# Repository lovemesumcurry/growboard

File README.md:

# growboard
 first keyboard PCB

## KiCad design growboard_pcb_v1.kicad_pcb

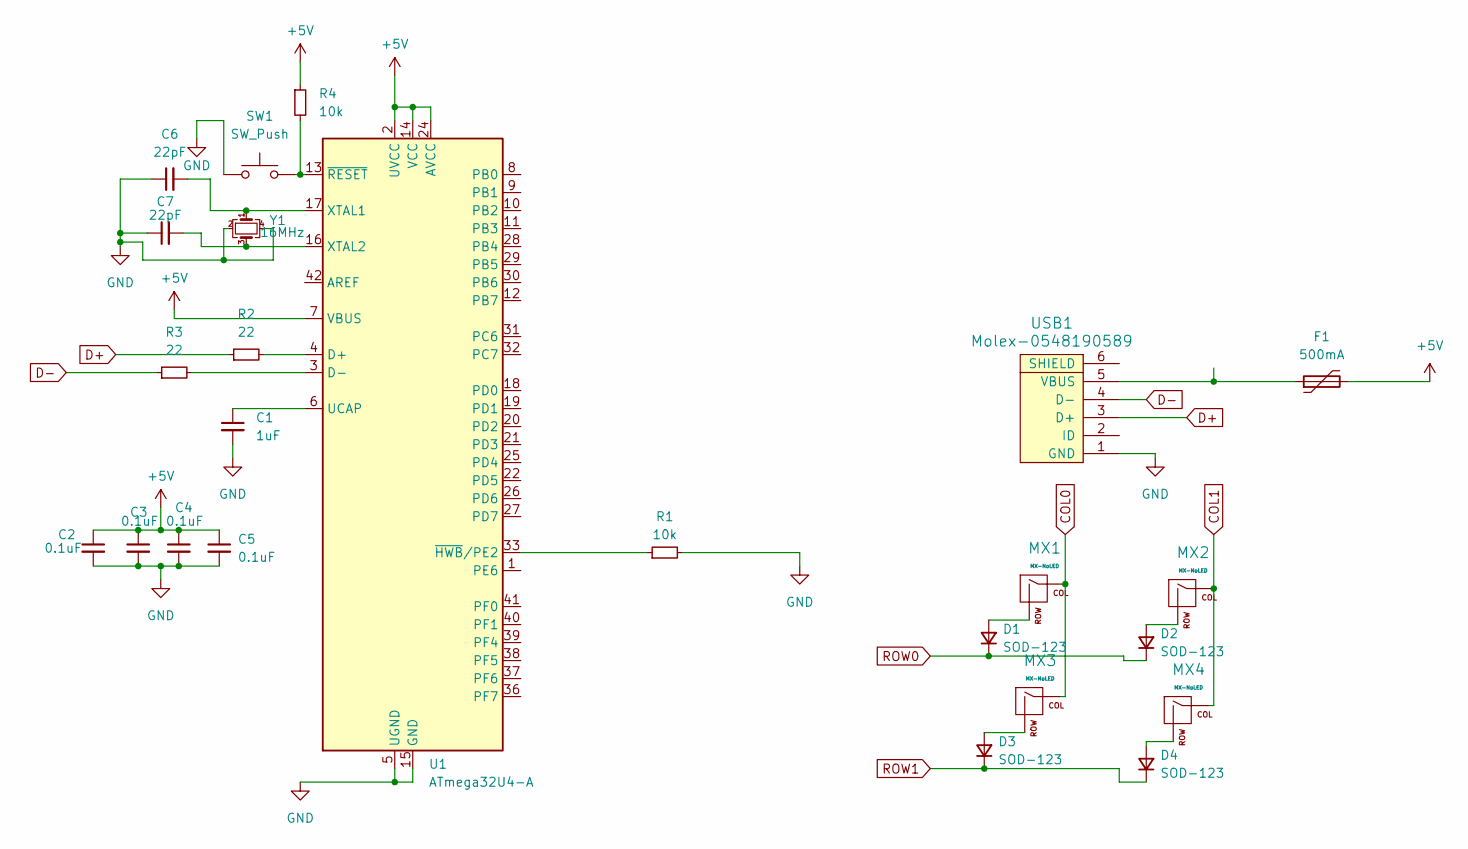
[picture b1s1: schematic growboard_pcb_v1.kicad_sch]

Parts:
C1: 1uF; C_0805_2012Metric
C2, C3, C4, C5: 0.1uF; C_0805_2012Metric
C6, C7: 22pF; C_0805_2012Metric
D1, D2, D3, D4: SOD-123; D_SOD-123
F1: 500mA; Fuse_1206_3216Metric
MX1, MX2, MX3, MX4: MX-NoLED; MX-1U-NoLED
R1, R4: 10k; R_0805_2012Metric
R2, R3: 22; R_0805_2012Metric
SW1: SW_Push; SKQG-1155865
U1: ATmega32U4-A; TQFP-44_10x10mm_P0.8mm
USB1: Molex-0548190589
Y1: 16MHz; Crystal_SMD_3225-4Pin_3.2x2.5mm

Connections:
+5V: C2.1, C3.1, C4.1, C5.1, F1.2, R4.1, U1.2 (UVCC), U1.7 (VBUS), U1.14 (VCC), U1.24 (AVCC), U1.34 (VCC), U1.44 (AVCC)
COL0: MX1.1 (COL), MX3.1 (COL)
COL1: MX2.1 (COL), MX4.1 (COL)
D+: R2.1, USB1.3 (D+)
D-: R3.1, USB1.4 (D-)
GND: C1.2, C2.2, C3.2, C4.2, C5.2, C6.1, C7.1, R1.2, SW1.1, U1.5 (UGND), U1.15 (GND), U1.23 (GND), U1.35 (GND), U1.43 (GND), USB1.1 (GND), Y1.2, Y1.4
unnamed: D1.2 (A), MX1.2 (ROW)
unnamed: D2.2 (A), MX2.2 (ROW)
unnamed: D3.2 (A), MX3.2 (ROW)
unnamed: D4.2 (A), MX4.2 (ROW)
unnamed: R2.2, U1.4 (D+)
unnamed: R3.2, U1.3 (D-)
unnamed: C1.1, U1.6 (UCAP)
unnamed: C6.2, U1.17 (XTAL1), Y1.1
unnamed: C7.2, U1.16 (XTAL2), Y1.3
unnamed: R1.1, U1.33 (~HWB/PE2)
unnamed: R4.2, SW1.2, U1.13 (~RESET)
unnamed: F1.1, USB1.5 (VBUS)
ROW0: D1.1 (K), D2.1 (K)
ROW1: D3.1 (K), D4.1 (K)

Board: 2 copper layers, 24 parts (0 on the bottom side), 20 nets, no tracks yet.

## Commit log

2023-11-07 initialize project
2023-11-07 Add footprint libraries
2023-11-07 Schematic built
2023-11-07 PCB without wiring
2023-11-11 PCB wiring
